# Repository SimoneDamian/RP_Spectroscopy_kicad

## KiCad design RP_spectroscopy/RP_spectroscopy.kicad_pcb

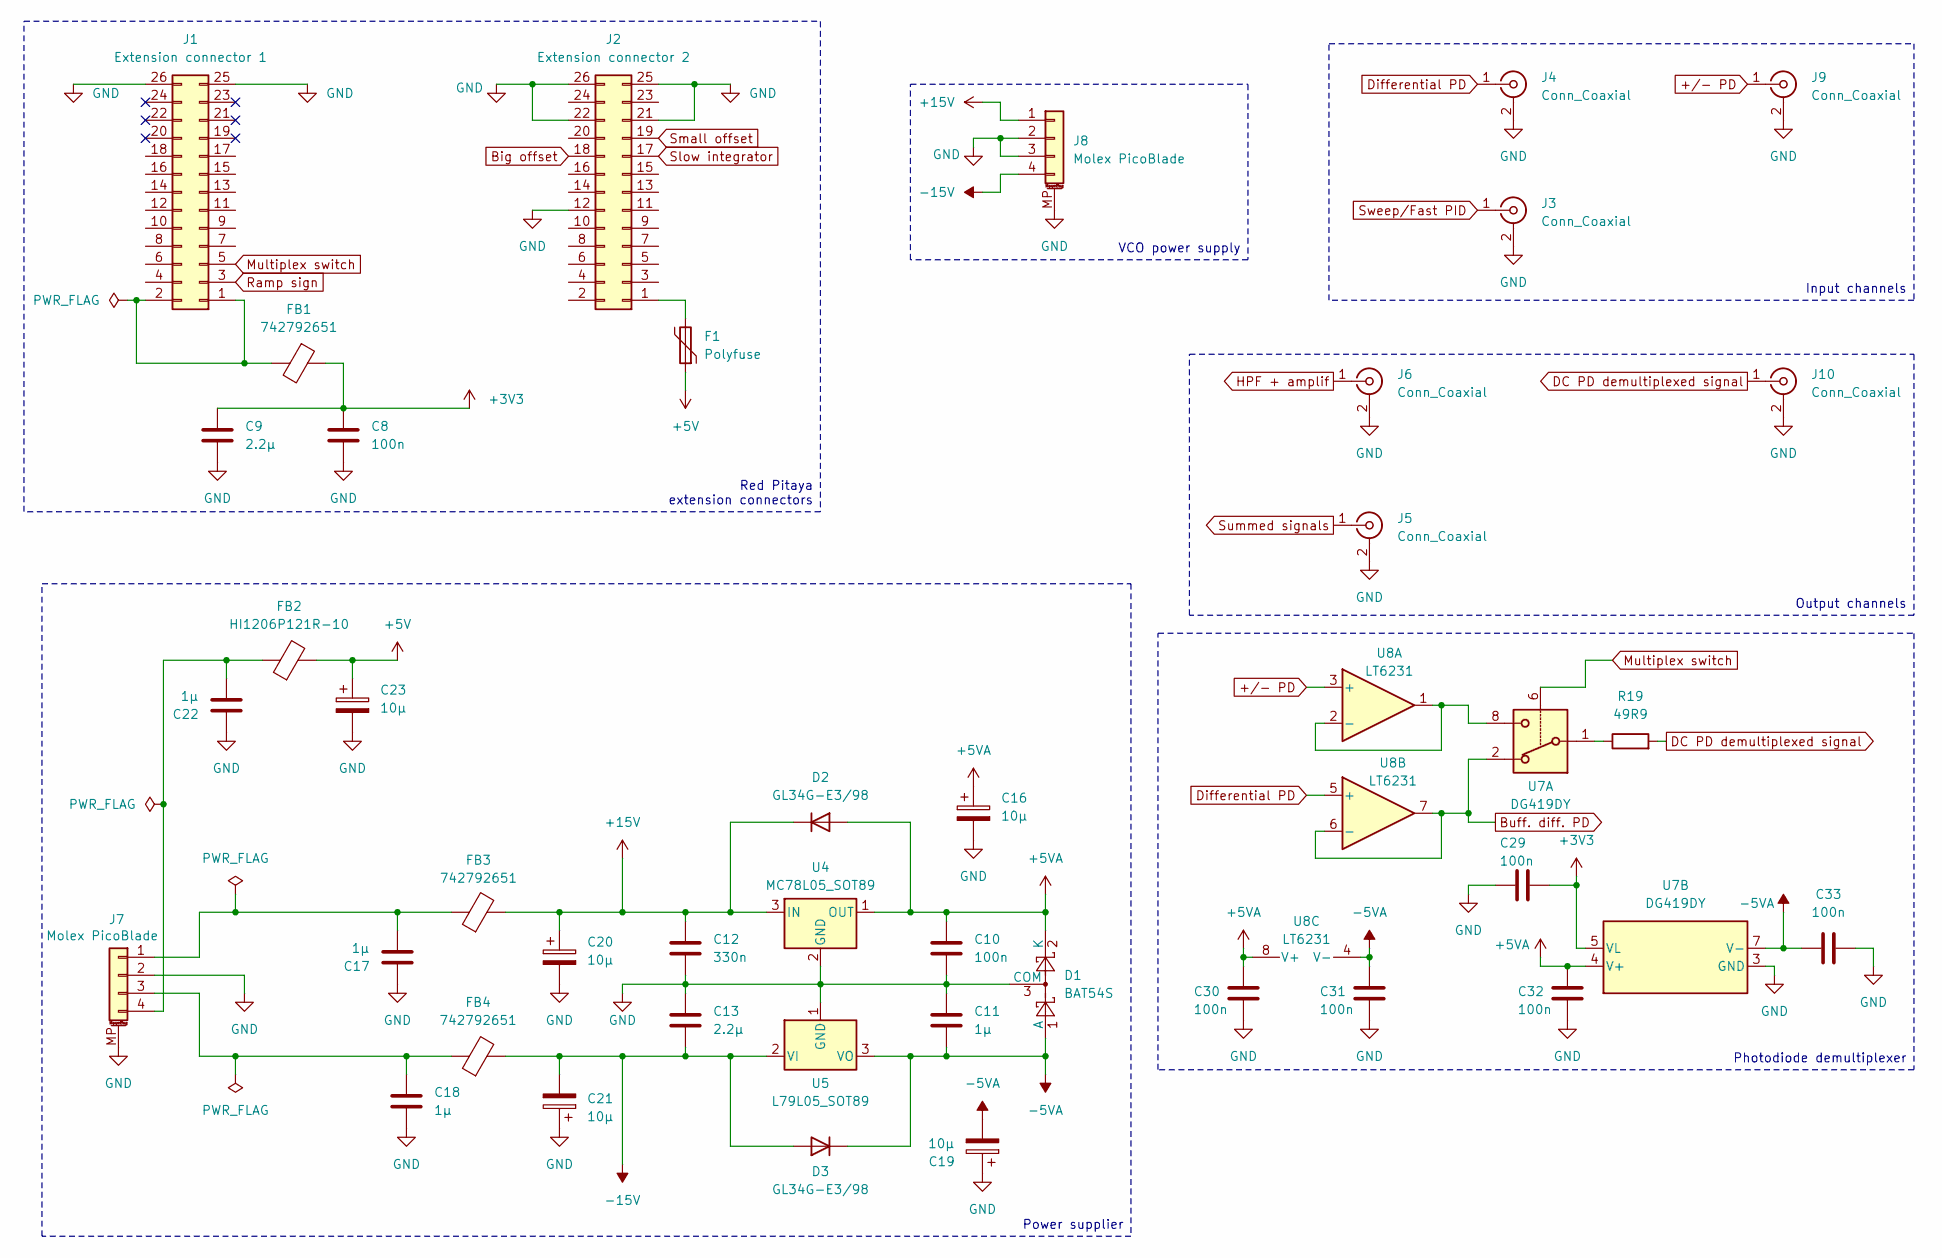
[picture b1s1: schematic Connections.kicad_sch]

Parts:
C8, C10, C29, C30, C31, C32, C33: 100n; C_0805_2012Metric_Pad1.18x1.45mm_HandSolder
C9, C13: 2.2µ; C_0805_2012Metric_Pad1.18x1.45mm_HandSolder
C11, C17, C18, C22: 1µ; C_0805_2012Metric_Pad1.18x1.45mm_HandSolder
C12: 330n; C_1206_3216Metric_Pad1.33x1.80mm_HandSolder
C16, C19, C20, C21, C23: 10µ; CP_Elec_6.3x5.7
D1: BAT54S; SOT-23
D2, D3: GL34G-E3/98; D_MicroMELF_Handsoldering
F1: Polyfuse; Fuse_0805_2012Metric_Pad1.15x1.40mm_HandSolder
FB1: 742792651; L_0603_1608Metric_Pad1.05x0.95mm_HandSolder
FB2: HI1206P121R-10; L_1206_3216Metric_Pad1.22x1.90mm_HandSolder
FB3, FB4: 742792651; L_0805_2012Metric_Pad1.05x1.20mm_HandSolder
J1: Extension connector 1; PinSocket_2x13_P2.54mm_Vertical
J2: Extension connector 2; PinSocket_2x13_P2.54mm_Vertical
J3, J4, J5, J6, J9, J10: Conn_Coaxial; SMA_Molex_73251-1153_EdgeMount_Horizontal
J7, J8: Molex PicoBlade; Molex_PicoBlade_53261-0471_1x04-1MP_P1.25mm_Horizontal
R19: 49R9; R_0805_2012Metric_Pad1.20x1.40mm_HandSolder
U4: MC78L05_SOT89; SOT-89-3_Handsoldering
U5: L79L05_SOT89; SOT-89-3_Handsoldering
U7: DG419DY; SOIC-8_3.9x4.9mm_P1.27mm
U8: LT6231; SOIC-8_3.9x4.9mm_P1.27mm

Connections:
+3V3: C8.1, C9.1, C29.1, FB1.1, U7.5 (VL); also elsewhere on the board
+5V: C23.1, F1.1, FB2.2
+5VA: C10.1, C16.1, C30.1, C32.1, D1.2 (K), D2.2 (A), U4.1 (OUT), U7.4 (V+), U8.8 (V+); also elsewhere on the board
+15V: C12.1, C20.1, D2.1 (K), FB3.2, J8.1, U4.3 (IN)
+/- PD: J9.1 (In), U8.3 (+)
-5VA: C11.2, C19.2, C31.1, C33.1, D1.1 (A), D3.1 (K), U5.3 (VO), U7.7 (V-), U8.4 (V-); also elsewhere on the board
-15V: C13.2, C21.2, D3.2 (A), FB4.2, J8.4, U5.2 (VI)
Big offset: J2.18; also elsewhere on the board
Buff. diff. PD: U7.2, U8.6 (-), U8.7; also elsewhere on the board
DC PD demultiplexed signal: J10.1 (In), R19.2
Differential PD: J4.1 (In), U8.5 (+)
GND: C8.2, C9.2, C10.2, C11.1, C12.2, C13.1, C16.2, C17.1, C18.2, C19.1, C20.2, C21.1, C22.1, C23.2, C29.2, C30.2, C31.2, C32.2, C33.2, D1.3 (COM), J1.25, J1.26, J2.12, J2.21, J2.22, J2.25, J2.26, J3.2 (Ext), J4.2 (Ext), J5.2 (Ext), J6.2 (Ext), J7.2, J7.MP (MountPin), J8.2, J8.3, J8.MP (MountPin), J9.2 (Ext), J10.2 (Ext), U4.2 (GND), U5.1 (GND), U7.3 (GND); also elsewhere on the board
HPF + amplif: J6.1 (In); also elsewhere on the board
Multiplex switch: J1.5, U7.6
unnamed: FB1.2, J1.1, J1.2
unnamed: F1.2, J2.1
unnamed: C17.2, FB3.1, J7.1
unnamed: C18.1, FB4.1, J7.3
unnamed: C22.2, FB2.1, J7.4
unnamed: R19.1, U7.1
unnamed: U7.8, U8.1, U8.2 (-)
Ramp sign: J1.3; also elsewhere on the board
Slow integrator: J2.17; also elsewhere on the board
Small offset: J2.19; also elsewhere on the board
Summed signals: J5.1 (In); also elsewhere on the board
Sweep/Fast PID: J3.1 (In); also elsewhere on the board

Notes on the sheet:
VCO power supply
Power supplier
Input channels
Red Pitaya extension connectors
Photodiode demultiplexer
Output channels

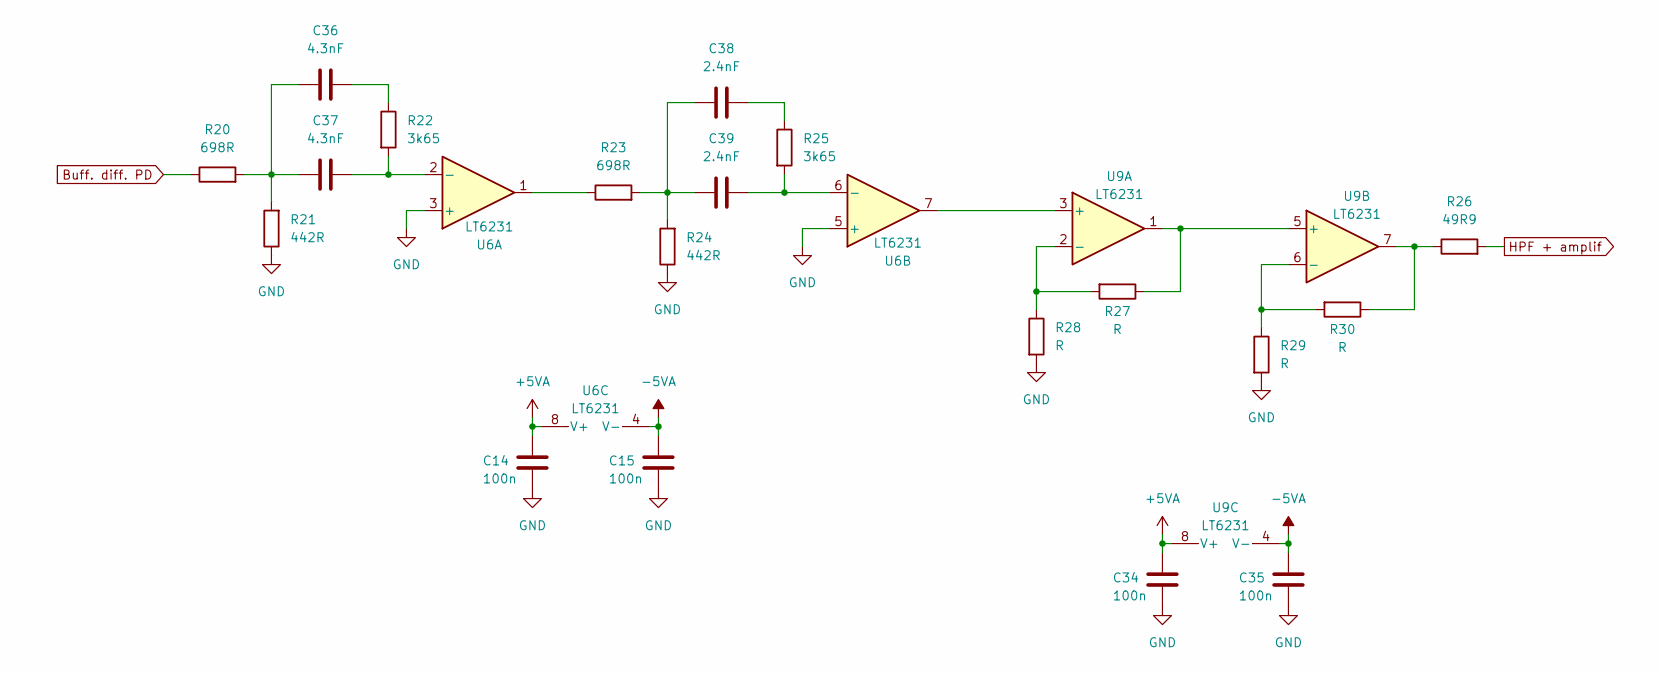
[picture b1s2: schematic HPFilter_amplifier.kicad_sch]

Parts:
C14, C15, C34, C35: 100n; C_0805_2012Metric_Pad1.18x1.45mm_HandSolder
C36, C37: 4.3nF; C_0805_2012Metric_Pad1.18x1.45mm_HandSolder
C38, C39: 2.4nF; C_0603_1608Metric_Pad1.08x0.95mm_HandSolder
R20, R23: 698R; R_0805_2012Metric_Pad1.20x1.40mm_HandSolder
R21, R24: 442R; R_0805_2012Metric_Pad1.20x1.40mm_HandSolder
R22, R25: 3k65; R_0805_2012Metric_Pad1.20x1.40mm_HandSolder
R26: 49R9; R_0805_2012Metric_Pad1.20x1.40mm_HandSolder
R27, R28, R29, R30: R; R_0805_2012Metric_Pad1.20x1.40mm_HandSolder
U6, U9: LT6231; SOIC-8_3.9x4.9mm_P1.27mm

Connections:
+5VA: C14.1, C34.1, U6.8 (V+), U9.8 (V+); also elsewhere on the board
-5VA: C15.1, C35.1, U6.4 (V-), U9.4 (V-); also elsewhere on the board
Buff. diff. PD: R20.1; also elsewhere on the board
GND: C14.2, C15.2, C34.2, C35.2, R21.1, R24.1, R28.2, R29.2, U6.3 (+), U6.5 (+); also elsewhere on the board
HPF + amplif: R26.2; also elsewhere on the board
unnamed: C36.1, C37.1, R20.2, R21.2
unnamed: C36.2, R22.1
unnamed: C38.1, C39.1, R23.2, R24.2
unnamed: C38.2, R25.1
unnamed: R23.1, U6.1
unnamed: R26.1, R30.1, U9.7
unnamed: C37.2, R22.2, U6.2 (-)
unnamed: C39.2, R25.2, U6.6 (-)
unnamed: U6.7, U9.3 (+)
unnamed: R27.2, R28.1, U9.2 (-)
unnamed: R27.1, U9.1, U9.5 (+)
unnamed: R29.1, R30.2, U9.6 (-)

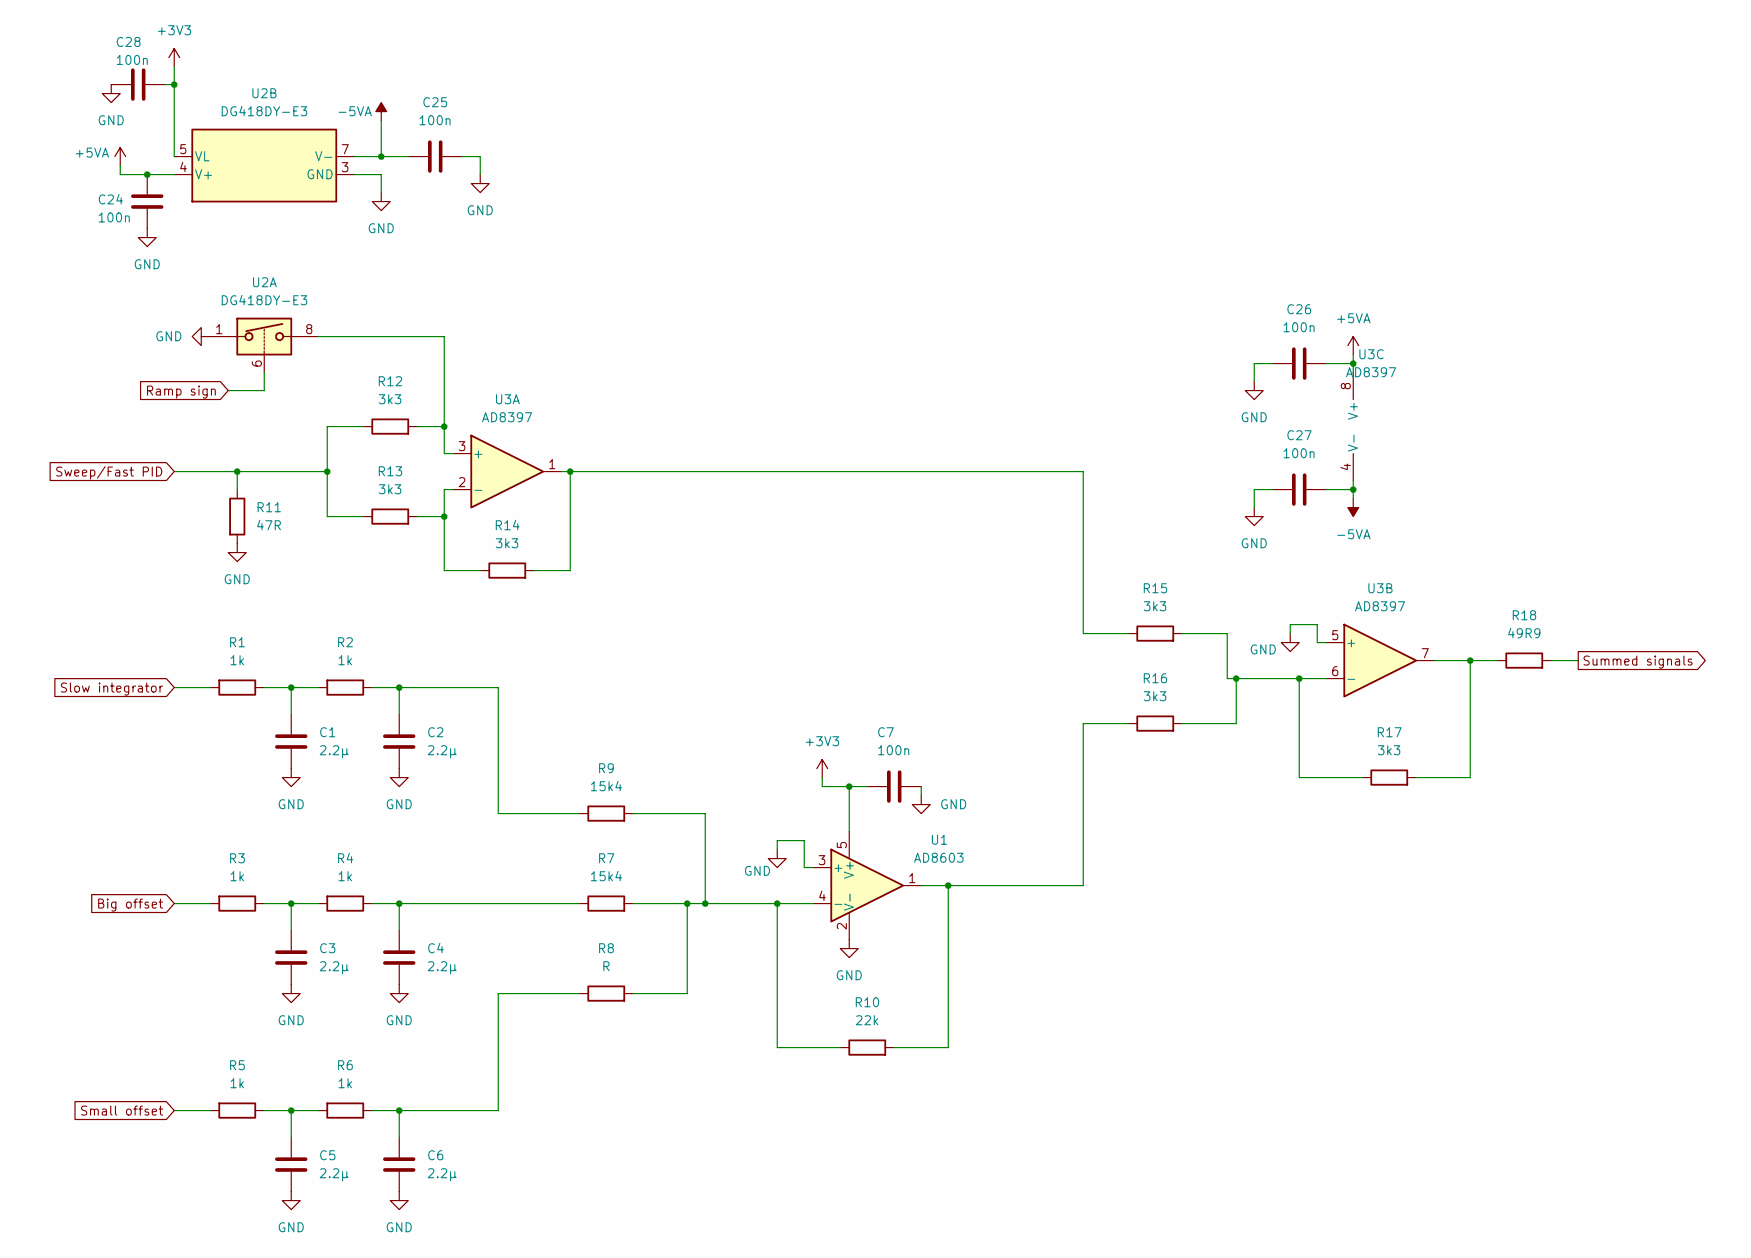
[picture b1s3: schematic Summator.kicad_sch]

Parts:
C1, C2, C3, C4, C5, C6: 2.2µ; C_0805_2012Metric_Pad1.18x1.45mm_HandSolder
C7, C24, C25, C26, C27, C28: 100n; C_0805_2012Metric_Pad1.18x1.45mm_HandSolder
R1, R2, R3, R4, R5, R6: 1k; R_0805_2012Metric_Pad1.20x1.40mm_HandSolder
R7, R9: 15k4; R_0805_2012Metric_Pad1.20x1.40mm_HandSolder
R8: R; R_0805_2012Metric_Pad1.20x1.40mm_HandSolder
R10: 22k; R_0805_2012Metric_Pad1.20x1.40mm_HandSolder
R11: 47R; R_0805_2012Metric_Pad1.20x1.40mm_HandSolder
R12, R13, R14, R15, R16, R17: 3k3; R_0805_2012Metric_Pad1.20x1.40mm_HandSolder
R18: 49R9; R_0805_2012Metric_Pad1.20x1.40mm_HandSolder
U1: AD8603; TSOT-23-5_HandSoldering
U2: DG418DY-E3; SOIC-8_3.9x4.9mm_P1.27mm
U3: AD8397; SOIC-8_3.9x4.9mm_P1.27mm

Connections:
+3V3: C7.1, C28.1, U1.5 (V+), U2.5 (VL); also elsewhere on the board
+5VA: C24.1, C26.2, U2.4 (V+), U3.8 (V+); also elsewhere on the board
-5VA: C25.1, C27.2, U2.7 (V-), U3.4 (V-); also elsewhere on the board
Big offset: R3.2; also elsewhere on the board
GND: C1.2, C2.2, C3.2, C4.2, C5.2, C6.2, C7.2, C24.2, C25.2, C26.1, C27.1, C28.2, R11.2, U1.2 (V-), U1.3 (+), U2.1, U2.3 (GND), U3.5 (+); also elsewhere on the board
unnamed: C1.1, R1.1, R2.2
unnamed: C2.1, R2.1, R9.1
unnamed: C3.1, R3.1, R4.2
unnamed: C4.1, R4.1, R7.1
unnamed: C5.1, R5.1, R6.2
unnamed: C6.1, R6.1, R8.1
unnamed: R10.2, R16.1, U1.1
unnamed: R14.2, R15.1, U3.1
unnamed: R17.2, R18.1, U3.7
unnamed: R7.2, R8.2, R9.2, R10.1, U1.4 (-)
unnamed: R12.2, U2.8, U3.3 (+)
unnamed: R13.2, R14.1, U3.2 (-)
unnamed: R15.2, R16.2, R17.1, U3.6 (-)
Ramp sign: U2.6; also elsewhere on the board
Slow integrator: R1.2; also elsewhere on the board
Small offset: R5.2; also elsewhere on the board
Summed signals: R18.2; also elsewhere on the board
Sweep/Fast PID: R11.1, R12.1, R13.1; also elsewhere on the board

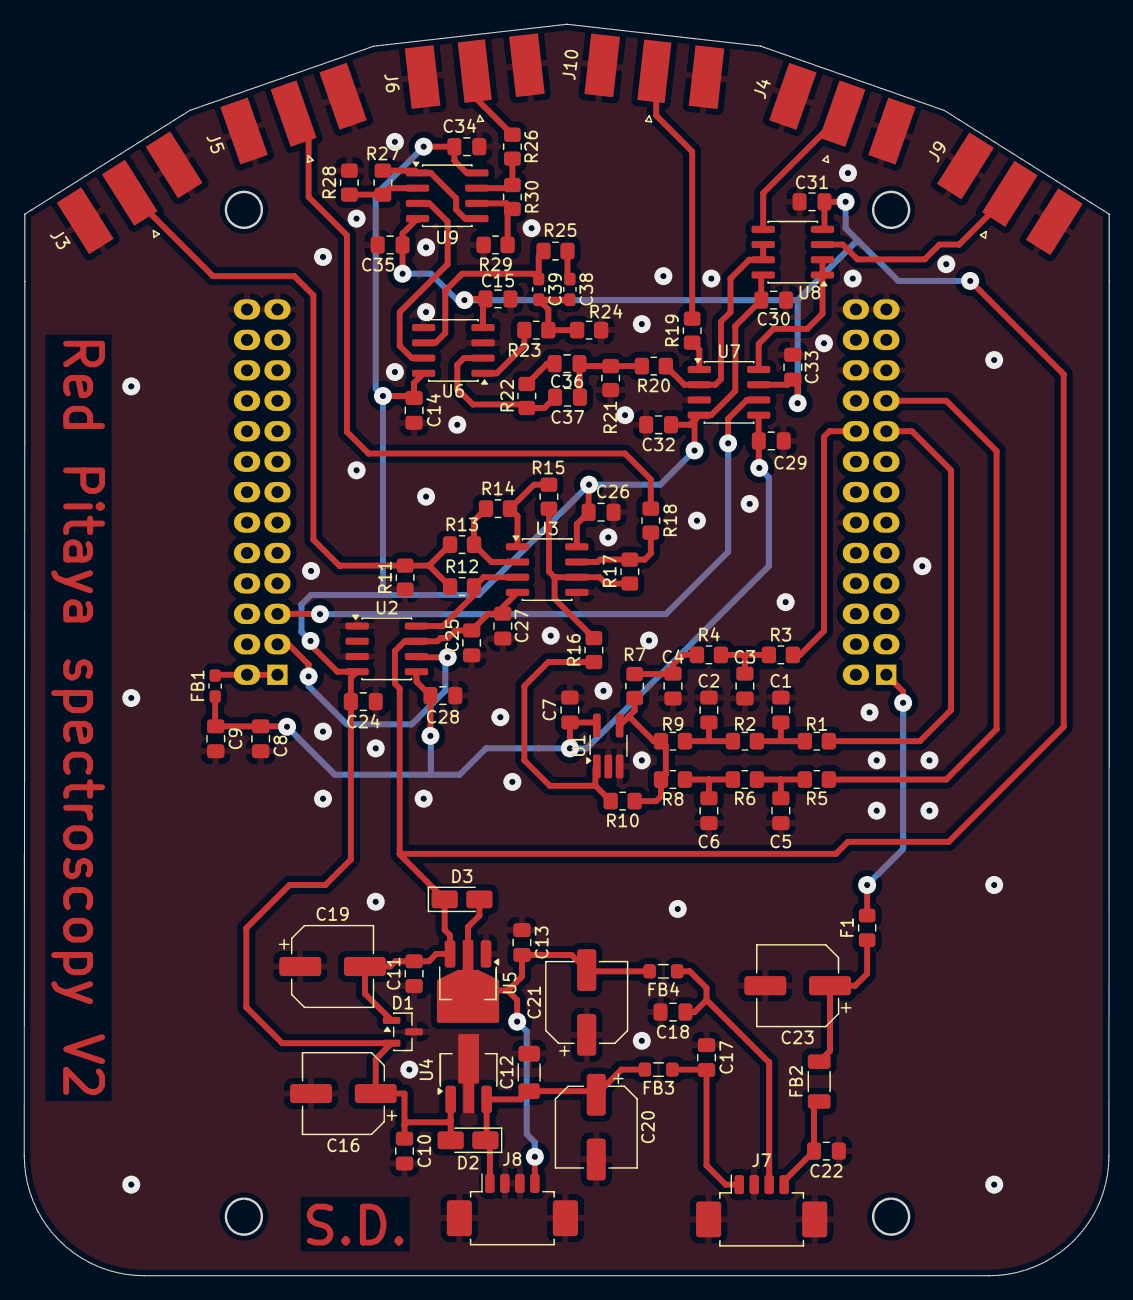
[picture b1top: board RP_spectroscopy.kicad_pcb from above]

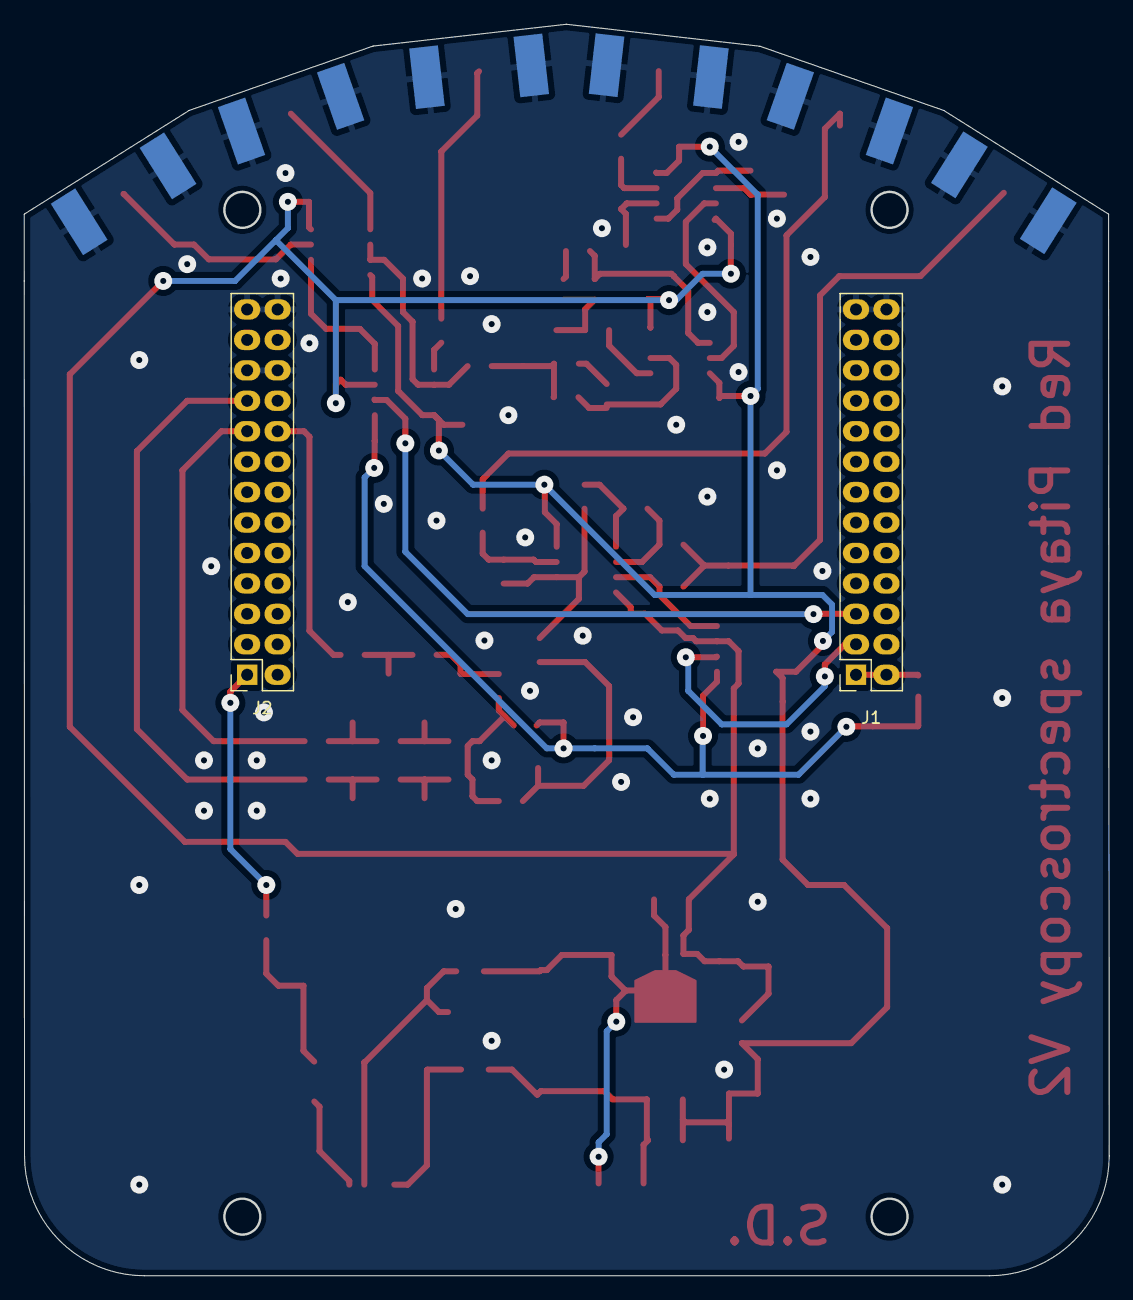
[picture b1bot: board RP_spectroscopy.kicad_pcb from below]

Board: 2 copper layers, 90.4 x 104.3 mm, 96 parts (2 on the bottom side), 51 nets.

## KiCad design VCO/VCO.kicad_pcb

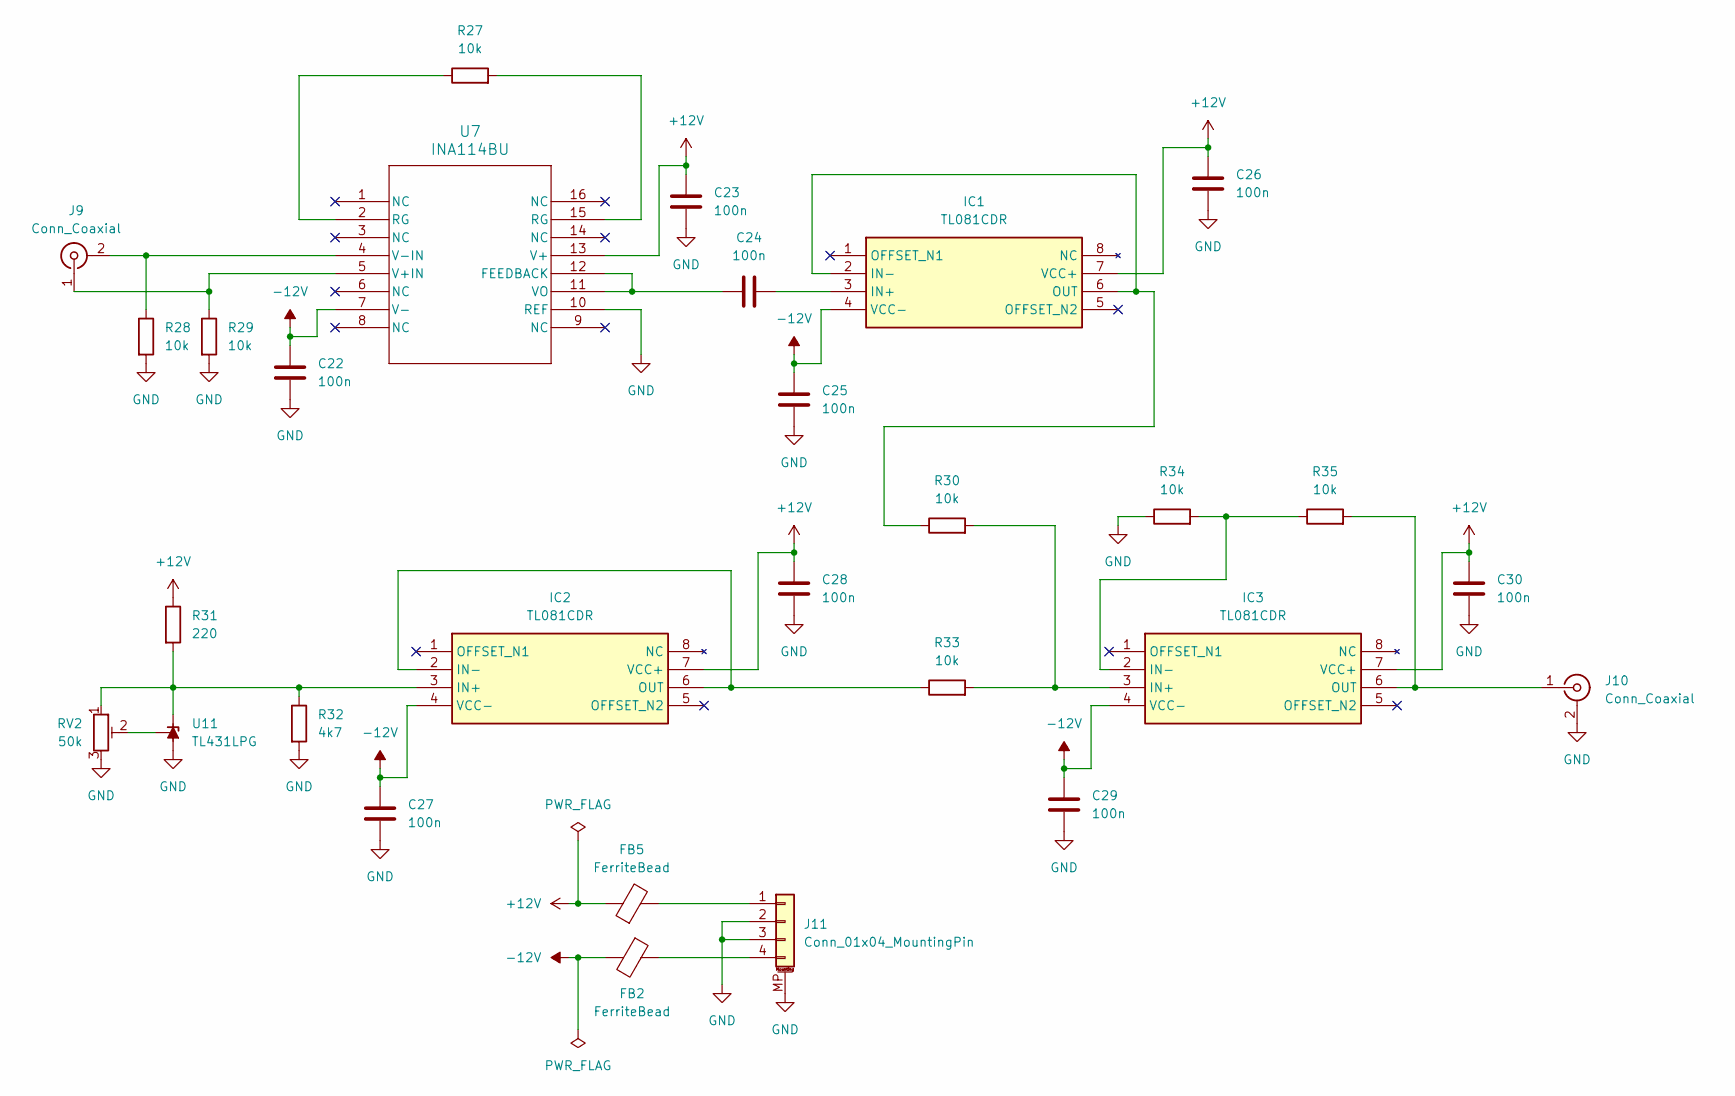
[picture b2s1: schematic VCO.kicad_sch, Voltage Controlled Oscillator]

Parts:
C22, C23, C24, C25, C26, C27, C28, C29, C30: 100n; C_0805_2012Metric_Pad1.18x1.45mm_HandSolder
FB2, FB5: FerriteBead; FerriteBread
IC1, IC2, IC3: TL081CDR; SOIC127P600X175-8N; Mouser Part Number 595-TL081CDR
J9, J10: Conn_Coaxial; SMA_Molex_73251-1153_EdgeMount_Horizontal
J11: Conn_01x04_MountingPin; Molex_PicoBlade_53261-0471_1x04-1MP_P1.25mm_Horizontal
R27, R28, R29, R30, R33, R34, R35: 10k; R_0805_2012Metric_Pad1.20x1.40mm_HandSolder
R31: 220; R_0805_2012Metric_Pad1.20x1.40mm_HandSolder
R32: 4k7; R_0805_2012Metric_Pad1.20x1.40mm_HandSolder
RV2: 50k; Potentiometer_Runtron_RM-063_Horizontal
U7: INA114BU; SOIC-16W_7.5x10.3mm_P1.27mm
U11: TL431LPG; TO-92_Inline

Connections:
+12V: C23.1, C26.1, C28.1, C30.1, FB5.1, IC1.7 (VCC+), IC2.7 (VCC+), IC3.7 (VCC+), R31.1, U7.13 (V+)
-12V: C22.1, C25.1, C27.1, C29.1, FB2.2, IC1.4 (VCC-), IC2.4 (VCC-), IC3.4 (VCC-), U7.7 (V-)
GND: C22.2, C23.2, C25.2, C26.2, C27.2, C28.2, C29.2, C30.2, J10.2 (Ext), J11.2, J11.3, J11.MP (MountPin), R28.2, R29.2, R32.2, R34.1, RV2.3, U7.10 (REF), U11.2 (A)
unnamed: C24.2, IC1.3 (IN+)
unnamed: IC1.2 (IN-), IC1.6 (OUT), R30.1
unnamed: IC2.3 (IN+), R31.2, R32.1, RV2.1, U11.3 (K)
unnamed: IC2.2 (IN-), IC2.6 (OUT), R33.1
unnamed: IC3.3 (IN+), R30.2, R33.2
unnamed: IC3.2 (IN-), R34.2, R35.1
unnamed: IC3.6 (OUT), J10.1 (In), R35.2
unnamed: J9.2 (Ext), R28.1, U7.4 (V-IN)
unnamed: J9.1 (In), R29.1, U7.5 (V+IN)
unnamed: FB5.2, J11.1
unnamed: FB2.1, J11.4
unnamed: R27.1, U7.2 (RG)
unnamed: R27.2, U7.15 (RG)
unnamed: C24.1, U7.11 (VO), U7.12 (FEEDBACK)
unnamed: RV2.2, U11.1 (REF)

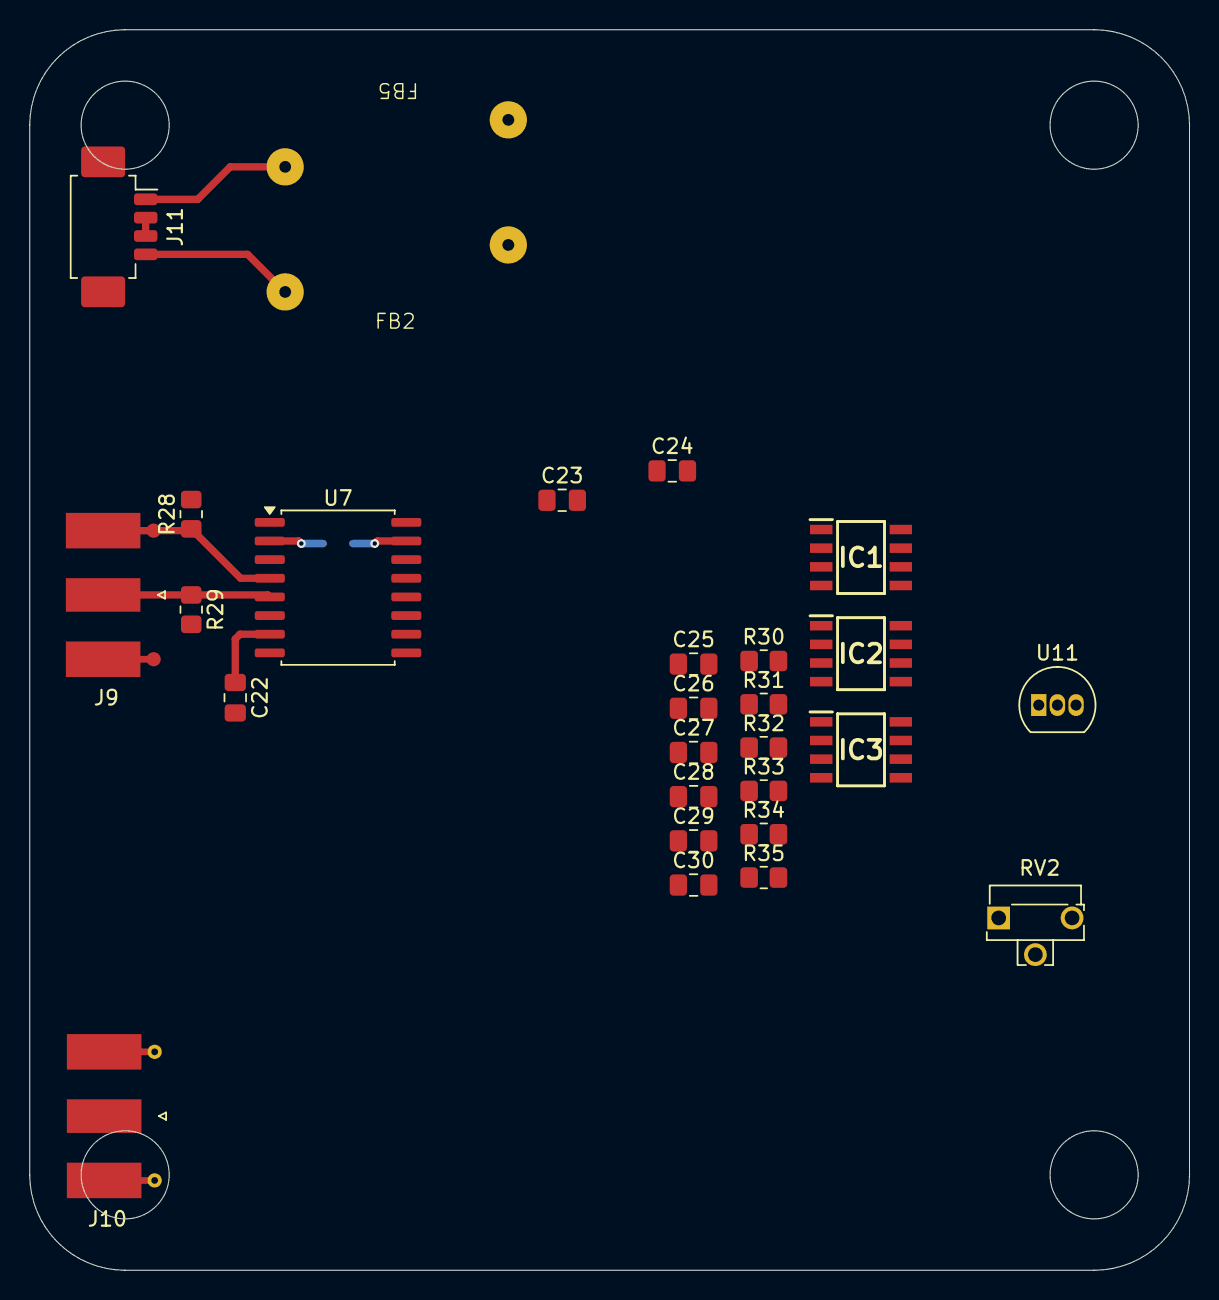
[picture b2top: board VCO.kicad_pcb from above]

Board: 2 copper layers, 79.0 x 84.5 mm, 29 parts (1 on the bottom side), 18 nets.

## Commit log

2026-03-21 Created the project and started to implement the connections and the summator circuit
2026-03-21 Almost finished the summator. Added also some components in the connectors schematic
2026-03-21 Continued with the connection scheet
2026-03-22 Added components to the power supply branch. Implemented the Sallen-Key filter + amplification branch.
2026-03-24 Added the VCO schematic and started to draw it.
2026-03-25 Implemented almost completely the VCO, apart from the VCO component itself
2026-03-29 Commit before deleting the VCO schematic from the main project. I have a separate project for that.
2026-03-29 Deleted the VCO part from the main project
2026-03-29 Added the EMI filter in the +5V branch and added the powerline capacitors for the remaining opamps. Removed the tunable offset from the summator. Assigned right footprints and specs to all the compon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
2026-03-30 Changed the way of implementing the powerline capacitors in order to find them easily while creating the pcb. Started implementing the double Sallen-Key filter.
2026-03-30 Started to implement the PCB
2026-03-31 Started to place all the components on the PCB. Simulated a bunch of filters.
2026-04-01 Additional modifications of parameters for produciton and some footprints
2026-04-03 Check of the availability of all the components and of the footprints. Added the demultiplexer part of the circuit. Some graphical changes. Changed the values of some R in order to match the ones ava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
2026-04-04 Added the summator parameters. Started to do the wireings
2026-04-04 Modified the input power connections in order to have the 5V to power the RP from the correct side
2026-04-04 Continued with the wireing of the PCB
2026-04-04 Finished the wirings of everything apart from the BP filter and amplification
2026-04-05 Modified the layout in order to give space in the upper part for the filter + amplification
2026-04-05 Compacted power and sumator branches. Started to check the RP measurement and compatibility
2026-04-05 Added the holes aligned with the ones of the RedPitaya. Modified the demultiplex circuit. Optimized the summator wireings.
2026-04-09 Added the BP filter and the amplification stages. It should be done.
2026-06-07 Project modified to solve the routing problems found while soldering
